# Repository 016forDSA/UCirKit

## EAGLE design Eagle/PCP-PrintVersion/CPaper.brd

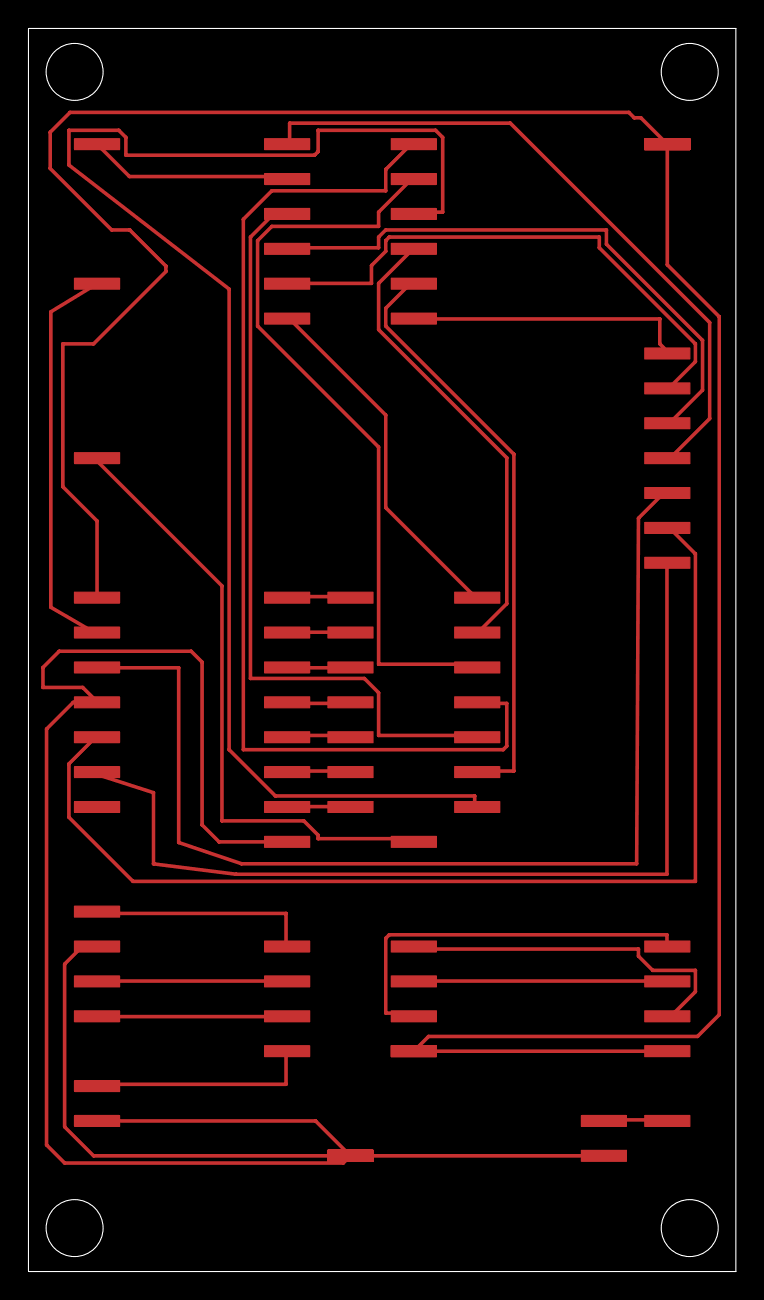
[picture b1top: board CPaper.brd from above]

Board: 2 copper layers, 49.7 x 87.3 mm, 82 parts (0 on the bottom side), 41 nets.

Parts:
JP1, JP2, JP3, JP4, JP5, JP6, JP7, JP8, JP9, JP10, JP11, JP12, JP13, JP14, JP15, JP16, JP17, JP18, JP19, JP20, JP21, JP22, JP23, JP24, JP25, JP26, JP27, JP28, JP29, JP30, JP31, JP32, JP33, JP34, JP35, JP36, JP37, JP38, JP39, JP40, JP41, JP42, JP43, JP44, JP45, JP46, JP47, JP48, JP49, JP50, JP51, JP52, JP53, JP54, JP55, JP56, JP57, JP58, JP59, JP60, JP61, JP62, JP63, JP64, JP65, JP66, JP67, JP68, JP69, JP70, JP71, JP72, JP73, JP74, JP75, JP76, JP77, JP78, JP79, JP80, JP81, JP82: 1X01_SMD_3.25X0.85MM_NO_SILK

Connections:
NEW_0: JP1.P$3, JP2.P$3
NEW_1: JP3.P$3, JP4.P$3
NEW_2: JP5.P$3, JP6.P$3
NEW_3: JP7.P$3, JP8.P$3
NEW_4: JP9.P$3, JP10.P$3
NEW_5: JP11.P$3, JP12.P$3
NEW_6: JP13.P$3, JP14.P$3
NEW_7: JP15.P$3, JP16.P$3
NEW_8: JP17.P$3, JP18.P$3
NEW_9: JP19.P$3, JP20.P$3
NEW_10: JP21.P$3, JP22.P$3
NEW_11: JP23.P$3, JP24.P$3
NEW_12: JP25.P$3, JP26.P$3
NEW_13: JP27.P$3, JP28.P$3
NEW_14: JP29.P$3, JP30.P$3
NEW_15: JP31.P$3, JP32.P$3
NEW_16: JP33.P$3, JP34.P$3
NEW_17: JP35.P$3, JP36.P$3
NEW_18: JP37.P$3, JP38.P$3
NEW_19: JP39.P$3, JP40.P$3
NEW_20: JP41.P$3, JP42.P$3
NEW_21: JP43.P$3, JP44.P$3
NEW_22: JP45.P$3, JP46.P$3
NEW_23: JP47.P$3, JP48.P$3
NEW_24: JP49.P$3, JP50.P$3
NEW_25: JP51.P$3, JP52.P$3
NEW_26: JP53.P$3, JP54.P$3
NEW_27: JP55.P$3, JP56.P$3
NEW_28: JP57.P$3, JP58.P$3
NEW_29: JP59.P$3, JP60.P$3
NEW_30: JP61.P$3, JP62.P$3
NEW_31: JP63.P$3, JP64.P$3
NEW_32: JP65.P$3, JP66.P$3
NEW_33: JP67.P$3, JP68.P$3
NEW_34: JP69.P$3, JP70.P$3
NEW_35: JP71.P$3, JP72.P$3
NEW_36: JP73.P$3, JP74.P$3
NEW_37: JP75.P$3, JP76.P$3
NEW_38: JP77.P$3, JP78.P$3
NEW_39: JP79.P$3, JP80.P$3
NEW_40: JP81.P$3, JP82.P$3

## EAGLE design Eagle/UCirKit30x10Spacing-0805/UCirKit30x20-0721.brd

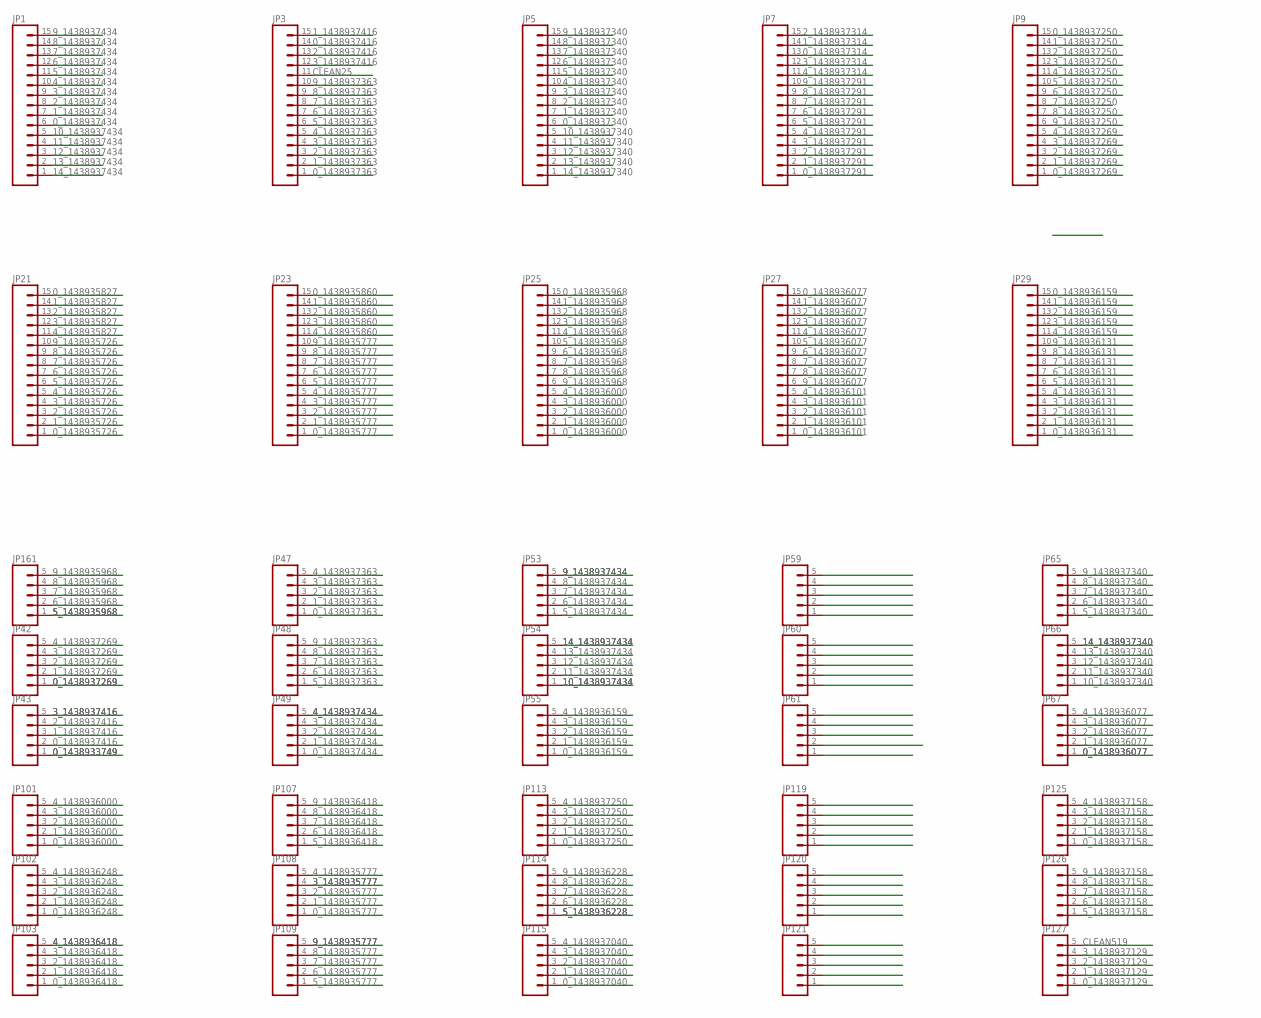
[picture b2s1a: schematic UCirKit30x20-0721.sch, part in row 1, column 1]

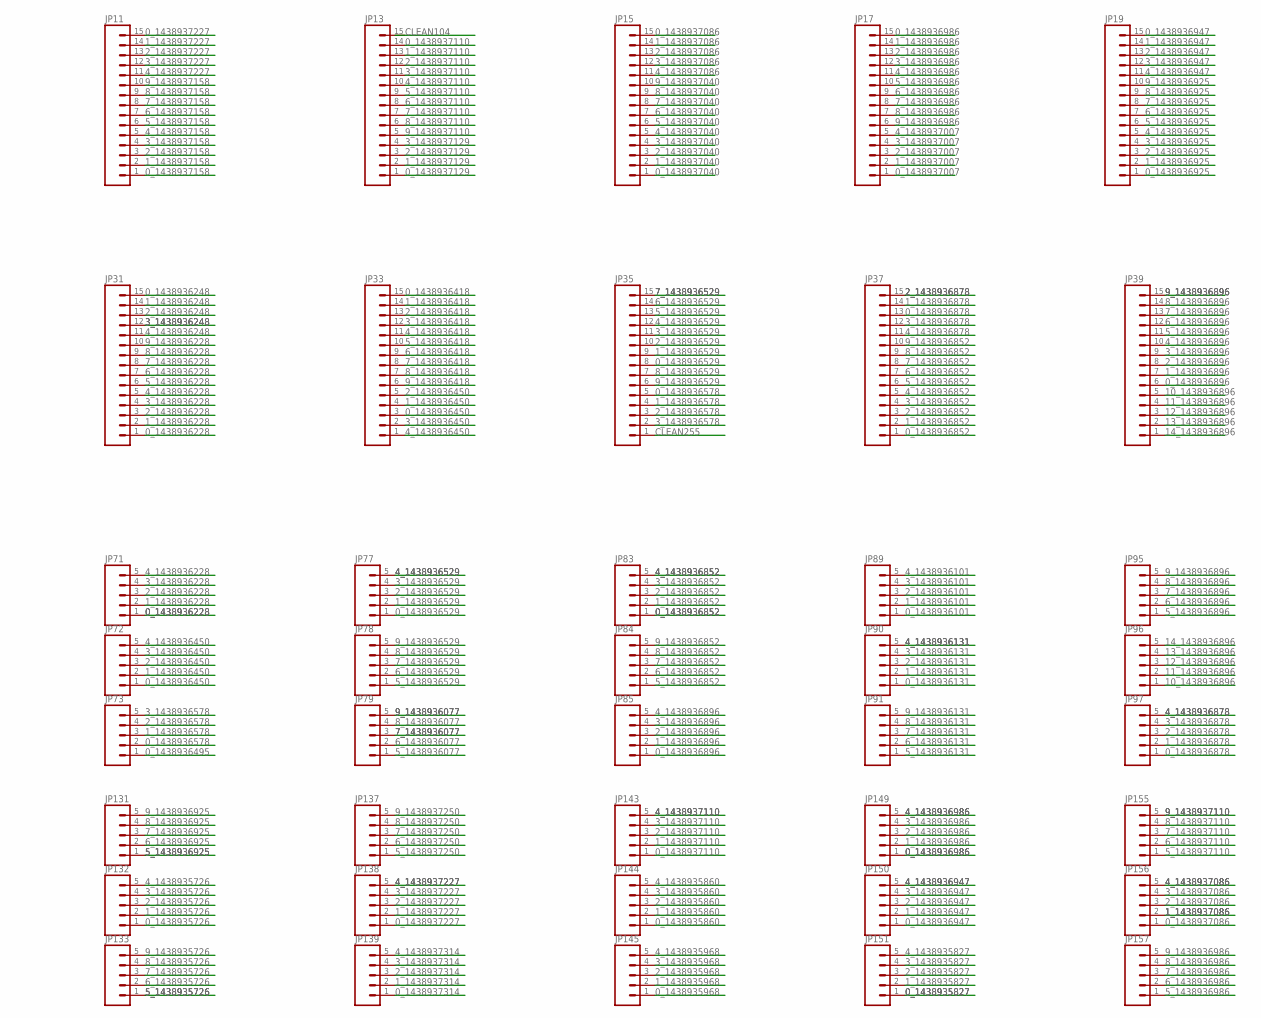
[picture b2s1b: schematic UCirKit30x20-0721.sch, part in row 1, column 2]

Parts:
JP1, JP3, JP5, JP7, JP9, JP11, JP13, JP15, JP17, JP19, JP21, JP23, JP25, JP27, JP29, JP31, JP33, JP35, JP37, JP39: M15; 1X15
JP42, JP43, JP47, JP48, JP49, JP53, JP54, JP55, JP59, JP60, JP61, JP65, JP66, JP67, JP71, JP72, JP73, JP77, JP78, JP79, JP83, JP84, JP85, JP89, JP90, JP91, JP95, JP96, JP97, JP101, JP102, JP103, JP107, JP108, JP109, JP113, JP114, JP115, JP119, JP120, JP121, JP125, JP126, JP127, JP131, JP132, JP133, JP137, JP138, JP139, JP143, JP144, JP145, JP149, JP150, JP151, JP155, JP156, JP157, JP161: M051.27MM; 1X05-1.27MM

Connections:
0_1438933749: JP43.1
0_1438935726: JP21.1, JP132.1
0_1438935777: JP23.1, JP108.1
0_1438935827: JP21.15, JP151.1
0_1438935860: JP23.15, JP144.1
0_1438935968: JP25.15, JP145.1
0_1438936000: JP25.1, JP101.1
0_1438936077: JP27.15, JP67.1
0_1438936101: JP27.1, JP89.1
0_1438936131: JP29.1, JP90.1
0_1438936159: JP29.15, JP55.1
0_1438936228: JP31.1, JP71.1
0_1438936248: JP31.15, JP102.1
0_1438936418: JP33.15, JP103.1
0_1438936450: JP33.3, JP72.1
0_1438936495: JP73.1
0_1438936529: JP35.8, JP77.1
0_1438936578: JP35.5, JP73.2
0_1438936852: JP37.1, JP83.1
0_1438936878: JP37.13, JP97.1
0_1438936896: JP39.6, JP85.1
0_1438936925: JP19.1, JP121.1
0_1438936947: JP19.15, JP150.1
0_1438936986: JP17.15, JP149.1
0_1438937007: JP17.1, JP120.1
0_1438937040: JP15.1, JP115.1
0_1438937086: JP15.15, JP156.1
0_1438937110: JP13.14, JP143.1
0_1438937129: JP13.1, JP127.1
0_1438937158: JP11.1, JP125.1
0_1438937227: JP11.15, JP138.1
0_1438937250: JP9.15, JP113.1
0_1438937269: JP9.1, JP42.1
0_1438937291: JP7.1, JP59.1
0_1438937314: JP7.13, JP139.1
0_1438937340: JP5.6, JP61.1
0_1438937363: JP3.1, JP47.1
0_1438937416: JP3.14, JP43.2
0_1438937434: JP1.6, JP49.1
1_1438935726: JP21.2, JP132.2
1_1438935777: JP23.2, JP108.2
1_1438935827: JP21.14, JP151.2
1_1438935860: JP23.14, JP144.2
1_1438935968: JP25.14, JP145.2
1_1438936000: JP25.2, JP101.2
1_1438936077: JP27.14, JP67.2
1_1438936101: JP27.2, JP89.2
1_1438936131: JP29.2, JP90.2
1_1438936159: JP29.14, JP55.2
1_1438936228: JP31.2, JP71.2
1_1438936248: JP31.14, JP102.2
1_1438936418: JP33.14, JP103.2
1_1438936450: JP33.4, JP72.2
1_1438936529: JP35.9, JP77.2
1_1438936578: JP35.4, JP73.3
1_1438936852: JP37.2, JP83.2
1_1438936878: JP37.14, JP97.2
1_1438936896: JP39.7, JP85.2
1_1438936925: JP19.2, JP121.2
1_1438936947: JP19.14, JP150.2
1_1438936986: JP17.14, JP149.2
1_1438937007: JP17.2, JP120.2
1_1438937040: JP15.2, JP115.2
1_1438937086: JP15.14, JP156.2
1_1438937110: JP13.13, JP143.2
1_1438937129: JP13.2, JP127.2
1_1438937158: JP11.2, JP125.2
1_1438937227: JP11.14, JP138.2
1_1438937250: JP9.14, JP113.2
1_1438937269: JP9.2, JP42.2
1_1438937291: JP7.2, JP59.2
1_1438937314: JP7.14, JP139.2
1_1438937340: JP5.7, JP61.2
1_1438937363: JP3.2, JP47.2
1_1438937416: JP3.15, JP43.3
1_1438937434: JP1.7, JP49.2
2_1438935726: JP21.3, JP132.3
2_1438935777: JP23.3, JP108.3
2_1438935827: JP21.13, JP151.3
2_1438935860: JP23.13, JP144.3
2_1438935968: JP25.13, JP145.3
2_1438936000: JP25.3, JP101.3
2_1438936077: JP27.13, JP67.3
2_1438936101: JP27.3, JP89.3
2_1438936131: JP29.3, JP90.3
2_1438936159: JP29.13, JP55.3
2_1438936228: JP31.3, JP71.3
2_1438936248: JP31.13, JP102.3
2_1438936418: JP33.13, JP103.3
2_1438936450: JP33.5, JP72.3
2_1438936529: JP35.10, JP77.3
2_1438936578: JP35.3, JP73.4
2_1438936852: JP37.3, JP83.3
2_1438936878: JP37.15, JP97.3
2_1438936896: JP39.8, JP85.3
2_1438936925: JP19.3, JP121.3
2_1438936947: JP19.13, JP150.3
2_1438936986: JP17.13, JP149.3
2_1438937007: JP17.3, JP120.3
2_1438937040: JP15.3, JP115.3
2_1438937086: JP15.13, JP156.3
2_1438937110: JP13.12, JP143.3
2_1438937129: JP13.3, JP127.3
2_1438937158: JP11.3, JP125.3
2_1438937227: JP11.13, JP138.3
2_1438937250: JP9.13, JP113.3
2_1438937269: JP9.3, JP42.3
2_1438937291: JP7.3, JP59.3
2_1438937314: JP7.15, JP139.3
2_1438937340: JP5.8, JP61.3
2_1438937363: JP3.3, JP47.3
2_1438937416: JP3.13, JP43.4
2_1438937434: JP1.8, JP49.3
3_1438935726: JP21.4, JP132.4
3_1438935777: JP23.4, JP108.4
3_1438935827: JP21.12, JP151.4
3_1438935860: JP23.12, JP144.4
3_1438935968: JP25.12, JP145.4
3_1438936000: JP25.4, JP101.4
3_1438936077: JP27.12, JP67.4
3_1438936101: JP27.4, JP89.4
3_1438936131: JP29.4, JP90.4
3_1438936159: JP29.12, JP55.4
3_1438936228: JP31.4, JP71.4
3_1438936248: JP31.12, JP102.4
3_1438936418: JP33.12, JP103.4
3_1438936450: JP33.2, JP72.4
3_1438936529: JP35.11, JP77.4
3_1438936578: JP35.2, JP73.5
3_1438936852: JP37.4, JP83.4
3_1438936878: JP37.12, JP97.4
3_1438936896: JP39.9, JP85.4
3_1438936925: JP19.4, JP121.4
3_1438936947: JP19.12, JP150.4
3_1438936986: JP17.12, JP149.4
3_1438937007: JP17.4, JP120.4
3_1438937040: JP15.4, JP115.4
3_1438937086: JP15.12, JP156.4
3_1438937110: JP13.11, JP143.4
3_1438937129: JP13.4, JP127.4
3_1438937158: JP11.4, JP125.4
3_1438937227: JP11.12, JP138.4
3_1438937250: JP9.12, JP113.4
3_1438937269: JP9.4, JP42.4
3_1438937291: JP7.4, JP59.4
3_1438937314: JP7.12, JP139.4
3_1438937340: JP5.9, JP61.4
3_1438937363: JP3.4, JP47.4
3_1438937416: JP3.12, JP43.5
3_1438937434: JP1.9, JP49.4
4_1438935726: JP21.5, JP132.5
4_1438935777: JP23.5, JP108.5
4_1438935827: JP21.11, JP151.5
4_1438935860: JP23.11, JP144.5
4_1438935968: JP25.11, JP145.5
4_1438936000: JP25.5, JP101.5
4_1438936077: JP27.11, JP67.5
4_1438936101: JP27.5, JP89.5
4_1438936131: JP29.5, JP90.5
4_1438936159: JP29.11, JP55.5
4_1438936228: JP31.5, JP71.5
4_1438936248: JP31.11, JP102.5
4_1438936418: JP33.11, JP103.5
4_1438936450: JP33.1, JP72.5
4_1438936529: JP35.12, JP77.5
4_1438936852: JP37.5, JP83.5
4_1438936878: JP37.11, JP97.5
4_1438936896: JP39.10, JP85.5
4_1438936925: JP19.5, JP121.5
4_1438936947: JP19.11, JP150.5
4_1438936986: JP17.11, JP149.5
4_1438937007: JP17.5, JP120.5
4_1438937040: JP15.5, JP115.5
4_1438937086: JP15.11, JP156.5
4_1438937110: JP13.10, JP143.5
4_1438937158: JP11.5, JP125.5
4_1438937227: JP11.11, JP138.5
4_1438937250: JP9.11, JP113.5
4_1438937269: JP9.5, JP42.5
4_1438937291: JP7.5, JP59.5
4_1438937314: JP7.11, JP139.5
4_1438937340: JP5.10, JP61.5
4_1438937363: JP3.5, JP47.5
4_1438937434: JP1.10, JP49.5
5_1438935726: JP21.6, JP133.1
5_1438935777: JP23.6, JP109.1
5_1438935968: JP25.10, JP161.1
5_1438936077: JP27.10, JP79.1
5_1438936131: JP29.6, JP91.1
5_1438936228: JP31.6, JP114.1
5_1438936418: JP33.10, JP107.1
5_1438936529: JP35.13, JP78.1
5_1438936852: JP37.6, JP84.1
5_1438936896: JP39.11, JP95.1
5_1438936925: JP19.6, JP131.1
5_1438936986: JP17.10, JP157.1
5_1438937040: JP15.6, JP119.1
5_1438937110: JP13.9, JP155.1
5_1438937158: JP11.6, JP126.1
5_1438937250: JP9.10, JP137.1
5_1438937291: JP7.6, JP60.1
5_1438937340: JP5.11, JP65.1
5_1438937363: JP3.6, JP48.1
5_1438937434: JP1.11, JP53.1
6_1438935726: JP21.7, JP133.2
6_1438935777: JP23.7, JP109.2
6_1438935968: JP25.9, JP161.2
6_1438936077: JP27.9, JP79.2
6_1438936131: JP29.7, JP91.2
6_1438936228: JP31.7, JP114.2
6_1438936418: JP33.9, JP107.2
6_1438936529: JP35.14, JP78.2
6_1438936852: JP37.7, JP84.2
6_1438936896: JP39.12, JP95.2
6_1438936925: JP19.7, JP131.2
6_1438936986: JP17.9, JP157.2
6_1438937040: JP15.7, JP119.2
6_1438937110: JP13.8, JP155.2
6_1438937158: JP11.7, JP126.2
6_1438937250: JP9.9, JP137.2
6_1438937291: JP7.7, JP60.2
6_1438937340: JP5.12, JP65.2
6_1438937363: JP3.7, JP48.2
6_1438937434: JP1.12, JP53.2
7_1438935726: JP21.8, JP133.3
7_1438935777: JP23.8, JP109.3
7_1438935968: JP25.8, JP161.3
7_1438936077: JP27.8, JP79.3
7_1438936131: JP29.8, JP91.3
7_1438936228: JP31.8, JP114.3
7_1438936418: JP33.8, JP107.3
7_1438936529: JP35.15, JP78.3
7_1438936852: JP37.8, JP84.3
7_1438936896: JP39.13, JP95.3
7_1438936925: JP19.8, JP131.3
7_1438936986: JP17.8, JP157.3
7_1438937040: JP15.8, JP119.3
7_1438937110: JP13.7, JP155.3
7_1438937158: JP11.8, JP126.3
7_1438937250: JP9.8, JP137.3
7_1438937291: JP7.8, JP60.3
7_1438937340: JP5.13, JP65.3
7_1438937363: JP3.8, JP48.3
7_1438937434: JP1.13, JP53.3
8_1438935726: JP21.9, JP133.4
8_1438935777: JP23.9, JP109.4
8_1438935968: JP25.7, JP161.4
8_1438936077: JP27.7, JP79.4
8_1438936131: JP29.9, JP91.4
8_1438936228: JP31.9, JP114.4
8_1438936418: JP33.7, JP107.4
8_1438936529: JP35.7, JP78.4
8_1438936852: JP37.9, JP84.4
8_1438936896: JP39.14, JP95.4
8_1438936925: JP19.9, JP131.4
8_1438936986: JP17.7, JP157.4
8_1438937040: JP15.9, JP119.4
8_1438937110: JP13.6, JP155.4
8_1438937158: JP11.9, JP126.4
8_1438937250: JP9.7, JP137.4
8_1438937291: JP7.9, JP60.4
8_1438937340: JP5.14, JP65.4
8_1438937363: JP3.9, JP48.4
8_1438937434: JP1.14, JP53.4
9_1438935726: JP21.10, JP133.5
9_1438935777: JP23.10, JP109.5
9_1438935968: JP25.6, JP161.5
9_1438936077: JP27.6, JP79.5
9_1438936131: JP29.10, JP91.5
9_1438936228: JP31.10, JP114.5
9_1438936418: JP33.6, JP107.5
9_1438936529: JP35.6, JP78.5
9_1438936852: JP37.10, JP84.5
9_1438936896: JP39.15, JP95.5
9_1438936925: JP19.10, JP131.5
9_1438936986: JP17.6, JP157.5
9_1438937040: JP15.10, JP119.5
9_1438937110: JP13.5, JP155.5
9_1438937158: JP11.10, JP126.5
9_1438937250: JP9.6, JP137.5
9_1438937291: JP7.10, JP60.5
9_1438937340: JP5.15, JP65.5
9_1438937363: JP3.10, JP48.5
9_1438937434: JP1.15, JP53.5
10_1438936896: JP39.5, JP96.1
10_1438937340: JP5.5, JP66.1
10_1438937434: JP1.5, JP54.1
11_1438936896: JP39.4, JP96.2
11_1438937340: JP5.4, JP66.2
11_1438937434: JP1.4, JP54.2
12_1438936896: JP39.3, JP96.3
12_1438937340: JP5.3, JP66.3
12_1438937434: JP1.3, JP54.3
13_1438936896: JP39.2, JP96.4
13_1438937340: JP5.2, JP66.4
13_1438937434: JP1.2, JP54.4
14_1438936896: JP39.1, JP96.5
14_1438937340: JP5.1, JP66.5
14_1438937434: JP1.1, JP54.5
CLEAN25: JP3.11
CLEAN255: JP35.1
CLEAN519: JP127.5

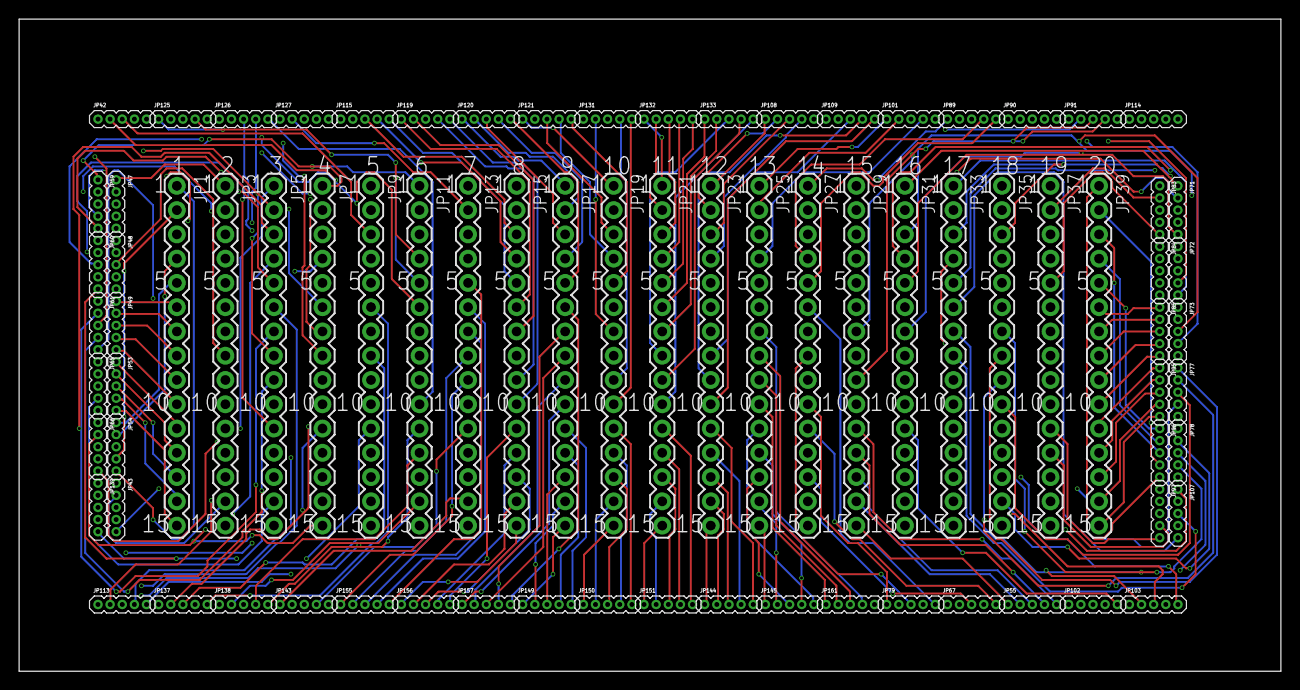
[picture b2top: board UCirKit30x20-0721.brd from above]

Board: 4 copper layers, 132.1 x 68.2 mm, 80 parts (0 on the bottom side), 297 nets.

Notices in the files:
parts and their libraries:
SparkFun-Connectors: Licensing: Creative Commons ShareAlike 4.0 International - https://creativecommons.org/licenses/by-sa/4.0
